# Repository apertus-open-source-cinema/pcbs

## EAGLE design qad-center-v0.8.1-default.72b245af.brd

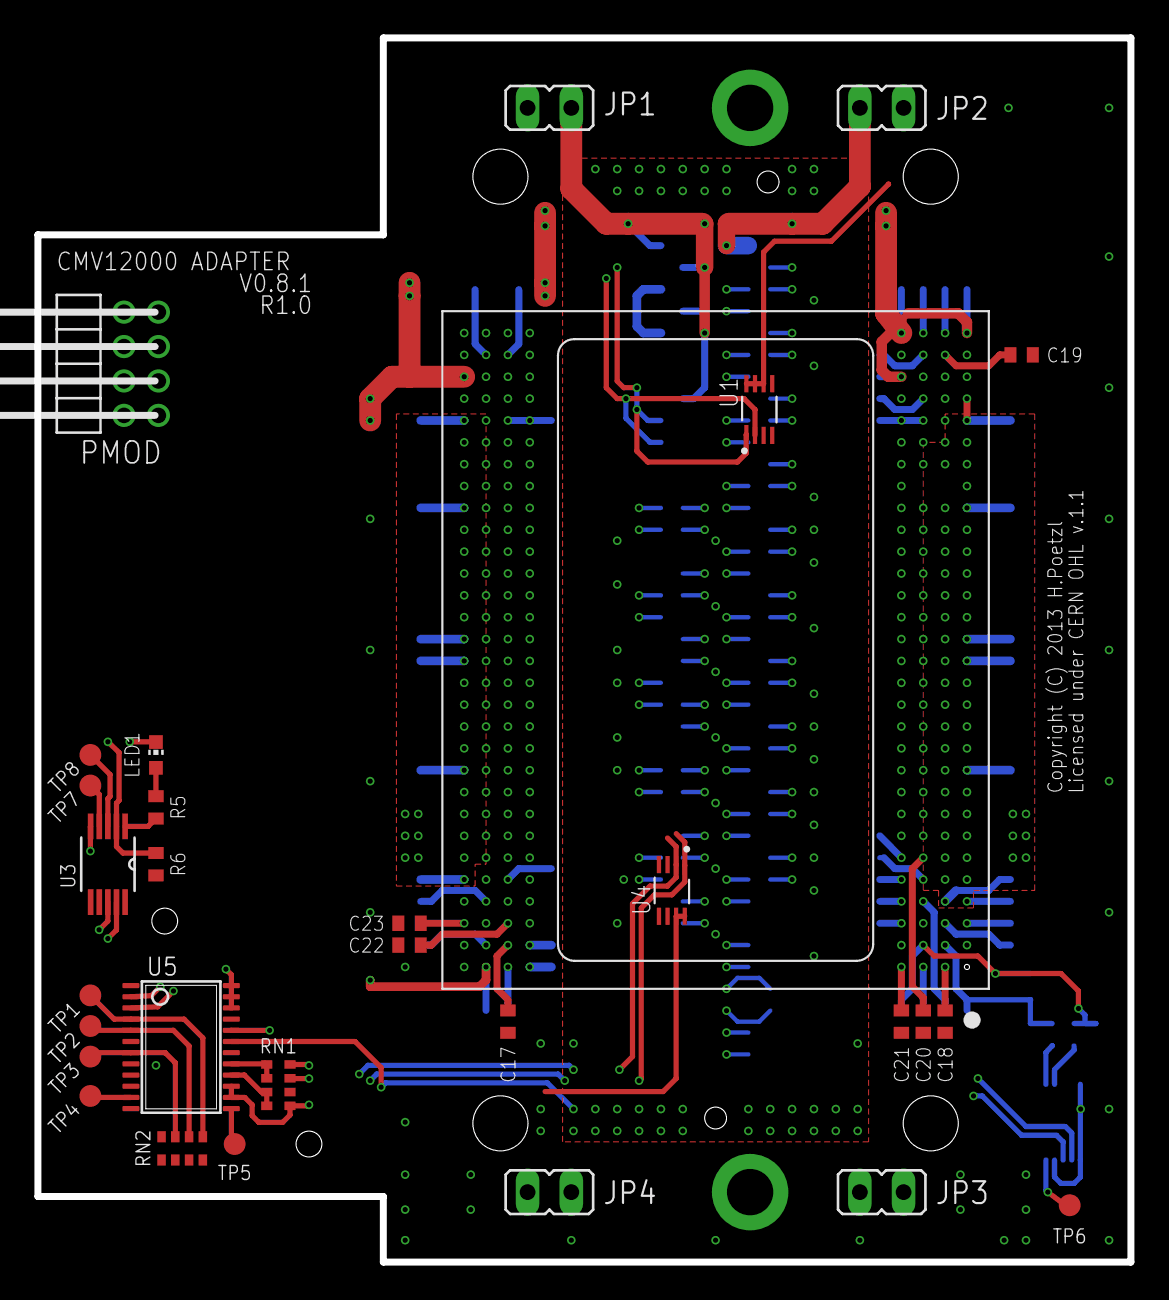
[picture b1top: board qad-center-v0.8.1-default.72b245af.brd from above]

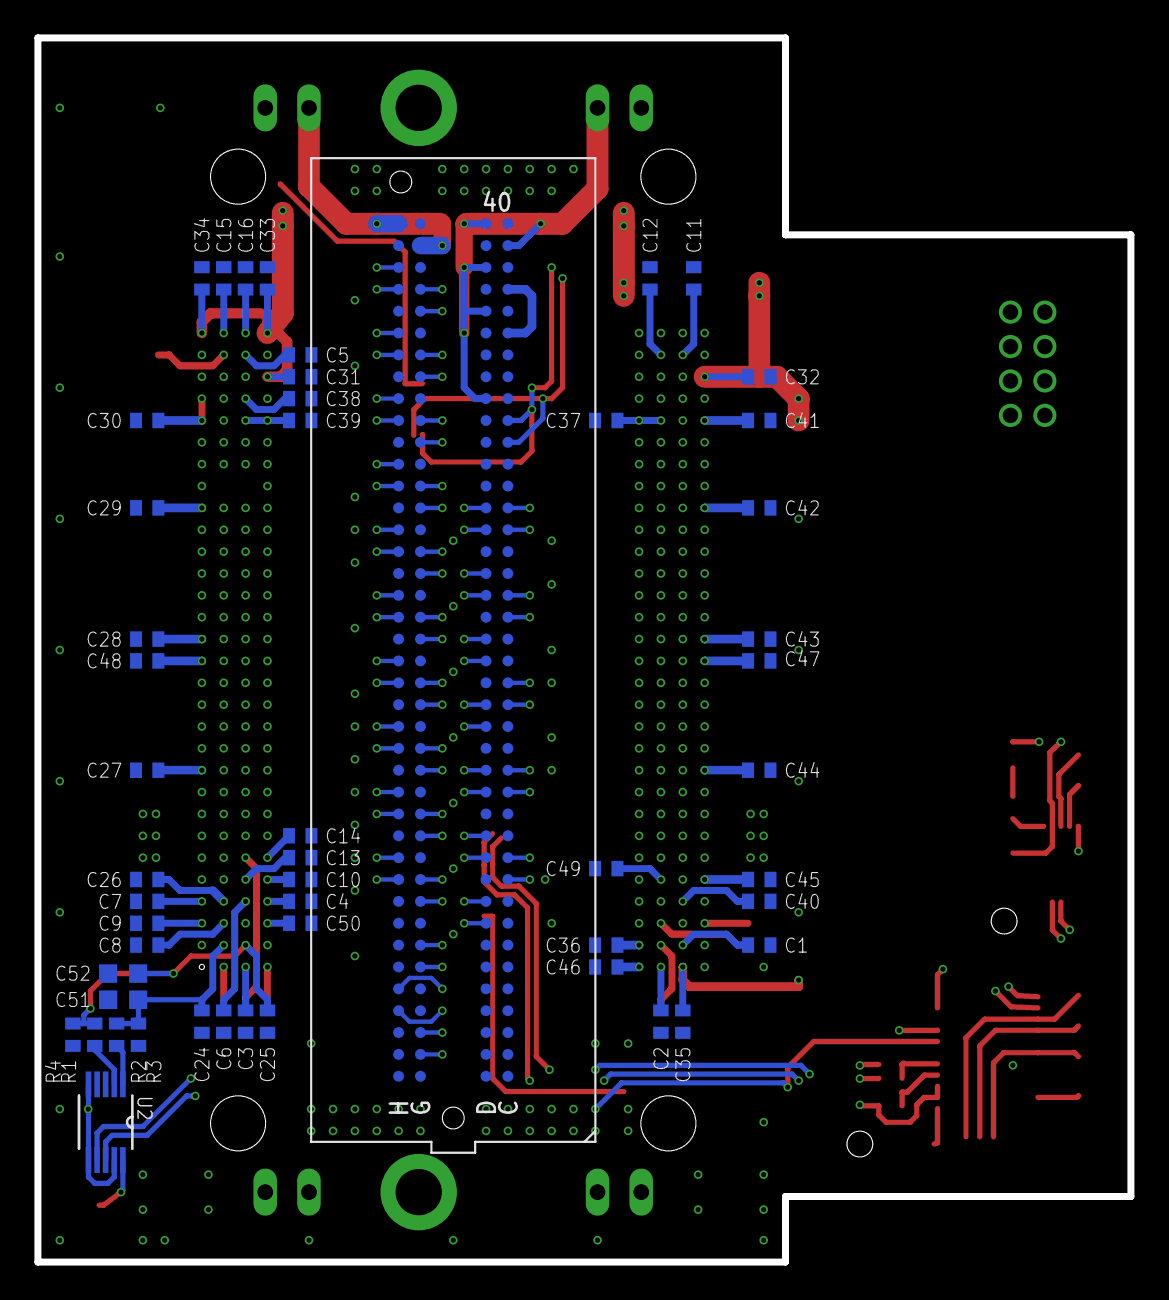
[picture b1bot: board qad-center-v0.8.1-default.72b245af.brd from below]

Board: 4 copper layers, 63.5 x 71.1 mm, 81 parts (50 on the bottom side), 129 nets.

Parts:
C1, C2, C3, C4, C5, C6, C7, C8, C9, C10, C11, C12, C13, C14, C15, C16, C17, C18, C19, C20, C21, C22, C23, C24, C25, C26, C27, C28, C29, C30, C32, C33, C34, C35, C36, C37, C38, C39, C40, C41, C42, C43, C44, C45, C46, C47, C48, C49, C50: C0402
C31: 100n; C0402
C51, C52: 10u; C0603K
JP1, JP2, JP3, JP4: JP1
LED1: RED; CHIP-LED0603
PMOD: PMOD-8; 2X04/90/2MM
R1, R2: 1R; R0402
R3, R4: R0402
R5: 220R; R0402
R6: 10k; R0402
RN1, RN2: 10k; CAT16
TP1, TP2, TP3, TP4, TP5, TP6, TP7, TP8: TPB1,27; B1,27
U1, U4: LM75BGD; SOT996-2/3
U2: AD5647R; SOP50P490X110-10N
U3: PCA9537; TSSOP-10
U5: LM96080; TSSOP24
U$1: CMV12000ANDON+LM; 10-30-07-237-400T4+LM
ZED1: FMC-LPC-ZED_NOCCZED; ASP-134604-01-ZED

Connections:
+1V8: JP2.2, JP3.1, JP4.1
+1V8A: C26.1, C27.1, C28.1, C29.1, C30.1, C48.1, JP3.2, U5.19, U$1.A10, U$1.A15, U$1.A16, U$1.A22, U$1.A26, U$1.A27, U$1.B4
+1V8B: C41.1, C42.1, C43.1, C44.1, C45.1, C46.1, C47.1, JP4.2, U5.20, U$1.E1, U$1.H5, U$1.H10, U$1.H15, U$1.H16, U$1.H22, U$1.H26
+3V0: C31.1, C32.1, C33.1, C34.1, C35.1, RN1.3, U$1.A30, U$1.D28, U$1.D30, U$1.G1, U$1.H28
+3V3: C17.1, C18.1, C19.1, C20.1, C21.1, C22.1, C23.1, C36.1, C37.1, C38.1, C39.1, C40.1, C49.1, C50.1, JP1.2, R6.1, RN1.2, RN2.2, RN2.3, RN2.4, U1.6, U1.7, U1.8, U2.5, U2.6, U2.9, U3.6, U3.10, U4.7, U4.8, U5.1, U5.6, U5.9, U5.12, U$1.C26, U$1.C27, U$1.D3, U$1.D26, U$1.E2, U$1.E26, U$1.F5, U$1.F26, U$1.G4
GND: C1.2, C2.2, C3.2, C4.2, C5.2, C6.2, C7.2, C8.2, C9.2, C10.2, C11.2, C12.2, C13.2, C14.2, C15.2, C16.2, C24.2, C25.2, C26.2, C27.2, C28.2, C29.2, C30.2, C31.2, C32.2, C33.2, C34.2, C35.2, C36.2, C37.2, C38.2, C39.2, C40.2, C41.2, C42.2, C43.2, C44.2, C45.2, C46.2, C47.2, C48.2, C49.2, C50.2, C51.2, C52.2, LED1.C, R3.2, R4.2, RN1.1, RN1.4, U1.4, U1.5, U2.3, U2.4, U3.5, U4.4, U4.5, U4.6, U5.8, U5.14, U5.15, U5.18, U5.21, U5.22, U5.23, U5.24, U$1.A9, U$1.A21, U$1.A25, U$1.A28, U$1.A29, U$1.B5, U$1.B22, U$1.B26, U$1.B27, U$1.B28, U$1.C15, U$1.C16, U$1.C28, U$1.D2, U$1.D25, U$1.D27, U$1.D29, U$1.E3, U$1.E15, U$1.E16, U$1.E25, U$1.E27, U$1.F27, U$1.G5, U$1.H1, U$1.H6, U$1.H9, U$1.H21, U$1.H25, U$1.H27, ZED1.C1, ZED1.C4, ZED1.C5, ZED1.C8, ZED1.C9, ZED1.C12, ZED1.C13, ZED1.C16, ZED1.C17, ZED1.C20, ZED1.C21, ZED1.C24, ZED1.C25, ZED1.C28, ZED1.C29, ZED1.C32, ZED1.C33, ZED1.C36, ZED1.C38, ZED1.C40, ZED1.D2, ZED1.D3, ZED1.D6, ZED1.D7, ZED1.D10, ZED1.D13, ZED1.D16, ZED1.D19, ZED1.D22, ZED1.D25, ZED1.D28, ZED1.D37, ZED1.D39, ZED1.G1, ZED1.G4, ZED1.G5, ZED1.G8, ZED1.G11, ZED1.G14, ZED1.G17, ZED1.G20, ZED1.G23, ZED1.G26, ZED1.G29, ZED1.G32, ZED1.G35, ZED1.G38, ZED1.G40, ZED1.H3, ZED1.H6, ZED1.H9, ZED1.H12, ZED1.H15, ZED1.H18, ZED1.H21, ZED1.H24, ZED1.H27, ZED1.H30, ZED1.H33, ZED1.H36, ZED1.H39
unnamed: C17.2, U$1.F2
unnamed: C18.2, U$1.B1
unnamed: C19.2, U$1.B29
unnamed: C20.2, U$1.C6
unnamed: C21.2, U$1.D1
unnamed: C22.2, U$1.F3
unnamed: C23.2, U$1.H3
unnamed: C1.1, U$1.G2
unnamed: C2.1, U$1.F1
unnamed: C3.1, U$1.C1
unnamed: C4.1, U$1.D4
unnamed: C5.1, U$1.C29
unnamed: C6.1, U$1.C4
unnamed: C7.1, U$1.A4
unnamed: C8.1, U$1.B3
unnamed: C9.1, U$1.A3
unnamed: C10.1, U$1.D5
unnamed: C11.1, U$1.G29
unnamed: C12.1, U$1.F29
unnamed: C13.1, U$1.C5
unnamed: C14.1, U$1.D6
unnamed: C15.1, U$1.B30
unnamed: C16.1, U$1.C30
unnamed: U$1.B6, ZED1.H11
unnamed: U$1.B7, ZED1.H10
unnamed: PMOD.1, U$1.F28
unnamed: U$1.D7, ZED1.D12
unnamed: U$1.D8, ZED1.D11
unnamed: PMOD.8, U$1.H29
unnamed: PMOD.2, U$1.E28
unnamed: PMOD.7, U$1.G28
unnamed: PMOD.10, U$1.E30
unnamed: PMOD.4, U$1.G30
unnamed: U$1.B8, ZED1.H14
unnamed: U$1.C9, ZED1.D15
unnamed: U$1.C10, ZED1.D14
unnamed: ZED1.C35, ZED1.C37
unnamed: JP1.1, ZED1.C39, ZED1.D32, ZED1.D36, ZED1.D38, ZED1.D40
unnamed: JP2.1, ZED1.G39, ZED1.H40
unnamed: R1.2, U2.2
unnamed: U$1.G10, ZED1.G13
unnamed: U$1.A11, ZED1.D18
unnamed: U$1.A12, ZED1.D17
unnamed: U$1.C11, ZED1.H17
unnamed: U$1.C12, ZED1.H16
unnamed: U$1.A13, ZED1.D21
unnamed: U$1.A14, ZED1.D20
unnamed: U$1.D13, ZED1.H20
unnamed: U$1.D14, ZED1.H19
unnamed: U$1.F16, ZED1.G22
unnamed: U$1.F17, ZED1.G21
unnamed: U$1.A17, ZED1.H26
unnamed: U$1.A18, ZED1.H25
unnamed: U$1.C17, ZED1.D24
unnamed: U$1.C18, ZED1.D23
unnamed: U$1.A19, ZED1.H29
unnamed: U$1.A20, ZED1.H28
unnamed: U$1.C19, ZED1.D27
unnamed: U$1.C20, ZED1.D26
unnamed: U$1.D21, ZED1.H32
unnamed: U$1.D22, ZED1.H31
unnamed: U$1.A23, ZED1.H35
unnamed: U$1.A24, ZED1.H34
unnamed: U$1.B24, ZED1.H38
unnamed: U$1.B25, ZED1.H37
unnamed: U$1.D15, ZED1.H23
unnamed: U$1.D16, ZED1.H22
unnamed: U$1.G22, ZED1.G34
unnamed: U$1.G23, ZED1.G33
unnamed: U$1.E22, ZED1.G30
unnamed: U$1.E21, ZED1.G31
unnamed: U$1.F21, ZED1.G27
unnamed: U$1.F20, ZED1.G28
unnamed: U$1.E20, ZED1.C26
unnamed: U$1.E19, ZED1.C27
unnamed: U$1.F19, ZED1.G24
unnamed: U$1.F18, ZED1.G25
unnamed: U$1.E18, ZED1.C22
unnamed: U$1.E17, ZED1.C23
unnamed: U$1.H23, ZED1.G37
unnamed: U$1.H24, ZED1.G36
unnamed: U$1.G15, ZED1.G18
unnamed: U$1.G14, ZED1.G19
unnamed: U$1.H14, ZED1.C18
unnamed: U$1.H13, ZED1.C19
unnamed: U$1.G13, ZED1.G15
unnamed: U$1.G12, ZED1.G16
unnamed: U$1.H12, ZED1.C14
unnamed: U$1.H11, ZED1.C15
unnamed: U$1.G11, ZED1.G12
unnamed: U$1.B9, ZED1.H13
unnamed: U$1.F9, ZED1.C10
unnamed: U$1.F8, ZED1.C11
unnamed: U$1.E8, ZED1.G9
unnamed: U$1.E7, ZED1.G10
unnamed: U$1.F7, ZED1.G6
unnamed: U$1.F6, ZED1.G7
unnamed: U$1.E5, ZED1.H5
unnamed: U$1.E6, ZED1.H4
unnamed: U$1.G6, ZED1.G3
unnamed: U$1.G7, ZED1.G2
unnamed: U$1.A5, ZED1.D9
unnamed: U$1.A6, ZED1.D8
unnamed: PMOD.9, U$1.H30
unnamed: PMOD.3, U$1.E29
unnamed: RN2.5, TP1.TP, U5.4
unnamed: R6.2, U3.2, U$1.F30
unnamed: R5.1, U3.1
unnamed: RN2.6, TP2.TP, U5.5
unnamed: TP8.TP, U3.3
unnamed: TP7.TP, U3.4
unnamed: RN1.5, RN1.6, U5.17
unnamed: RN2.7, TP3.TP, U5.7
unnamed: TP4.TP, U5.11
unnamed: TP5.TP, U5.13
unnamed: RN1.7, RN1.8, U5.16
unnamed: R2.2, U2.1
unnamed: LED1.A, R5.2
unnamed: TP6.TP, U2.10
SCL: U1.2, U2.7, U3.8, U4.2, U5.3, ZED1.C30
SDA: U1.1, U2.8, U3.9, U4.1, U5.2, ZED1.C31
VTREF: C24.1, C51.1, R2.1, R3.1, U$1.B2
VTSIG: C25.1, C52.1, R1.1, R4.1, U$1.C2

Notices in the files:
qad-center-v0.8.1-default.72b245af.brd:
Copyright (C) 2013 H.Poetzl
Licensed under CERN OHL v.1.1
